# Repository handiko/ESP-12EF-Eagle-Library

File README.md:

# ESP-12E/F Eagle Library
Eagle library for the barebone ESP-12E/F WiFi modules.
ESP-12E/F datasheet can be found on [kloppenborg.net](https://www.kloppenborg.net/images/blog/esp8266/esp8266-esp12e-specs.pdf) or [from elecrow.com](https://www.elecrow.com/download/ESP-12F.pdf)

## Installation
### Linux
* `git clone https://github.com/handiko//ESP-12EF-Eagle-Library.git`
* `cd /ESP-12EF-Eagle-Library/lbr`
* Copy the `esp-12e-f.lbr` into your Eagle library folder. For example, if your eagle library folder is located in `/opt/eagle-7.2.0/lbr`, then type: `sudo cp esp-12e-f.lbr /opt/eagle-7.2.0/lbr`
* Open the Eagle CAD, then **Library ---> Use All**
* Now the esp12e.lbr should be listed in your Eagle library.

### Windows
* Download as zip
* Unzip
* copy the `esp-12e-f.lbr` from **\ESP-12EF-Eagle-Library\lbr** into your Eagle library folder, for example : **C:\EAGLE-7.2.0\lbr**
* Open the Eagle CAD, then **Library --> Use All**

## Example
Breakout board, 22 pins, standard 0.1 inch pin connector, single layer top copper PCB.

## TODO
* Make a better example sch / board
* Adding description to the Device
* Better documentation / README
* ...

## Contributing
1. Fork it (https://github.com/handiko/ESP-12EF-Eagle-Library/fork)
2. Create new branch (`git checkout -b myfeature`)
3. Do some editing / create new feature
4. Commit your works (`git commit -m "Adding some myfeature blah blah blah.."`)
5. Push to the branch (`git push -u origin myfeature`)
6. Create a new Pull Request

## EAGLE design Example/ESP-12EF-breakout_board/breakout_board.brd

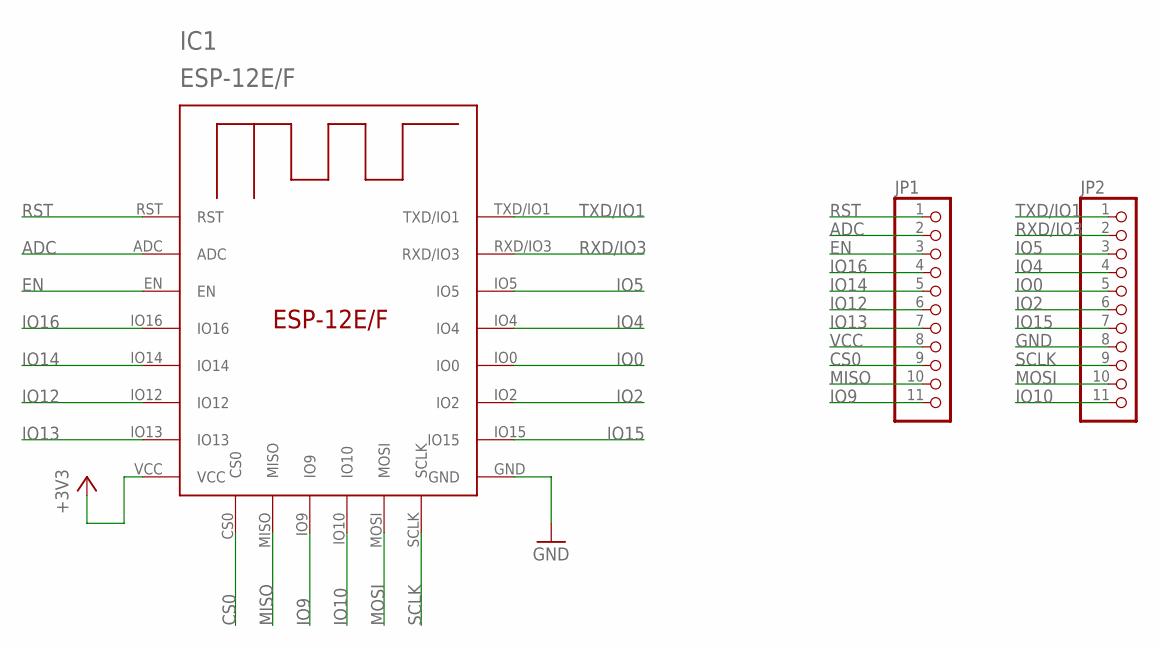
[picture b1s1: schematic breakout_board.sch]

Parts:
IC1: ESP-12E/F; ESP-12E
JP1, JP2: PINHD-1X11; 1X11

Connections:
ADC: IC1.ADC, JP1.2
CS0: IC1.CS0, JP1.9
EN: IC1.EN, JP1.3
GND: IC1.GND, JP2.8
IO0: IC1.IO0, JP2.5
IO2: IC1.IO2, JP2.6
IO4: IC1.IO4, JP2.4
IO5: IC1.IO5, JP2.3
IO9: IC1.IO9, JP1.11
IO10: IC1.IO10, JP2.11
IO12: IC1.IO12, JP1.6
IO13: IC1.IO13, JP1.7
IO14: IC1.IO14, JP1.5
IO15: IC1.IO15, JP2.7
IO16: IC1.IO16, JP1.4
MISO: IC1.MISO, JP1.10
MOSI: IC1.MOSI, JP2.10
RST: IC1.RST, JP1.1
RXD/IO3: IC1.RXD/IO3, JP2.2
SCLK: IC1.SCLK, JP2.9
TXD/IO1: IC1.TXD/IO1, JP2.1
VCC: IC1.VCC, JP1.8

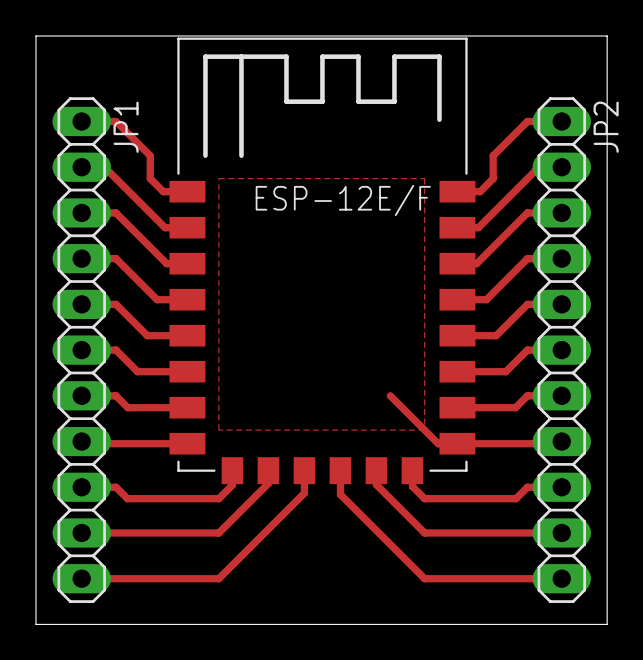
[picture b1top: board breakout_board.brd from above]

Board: 2 copper layers, 31.7 x 32.7 mm, 3 parts (0 on the bottom side), 22 nets.

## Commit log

2019-01-19 Set theme jekyll-theme-cayman
2019-01-19 Rename README.md to README2.md
2019-01-19 Create LICENSE
2019-01-19 Adding .gitignore
2019-01-19 Adding example
2019-01-19 adding pics
